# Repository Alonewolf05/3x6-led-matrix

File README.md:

# 3x6-led-matrix
High Power Led Matrix Schematic and PCB Design

Using transistors, shift registers can be used for high power LED applications.

There are 8 pins and micro usb type-b inputs for this board. USB is just for powering the board. No data tranferrings.
ICs are SN74HC595 modules with SOIC127 package.

Pin | Pin Description
------------ | -------------
1 | SRCLK for IC2
2 | SRCLK for IC1
3 | RCLK for IC2
4 | RCLK for IC1
5 | SER for IC2
6 | SER for IC1
7 | GND
8 | +5V

With IC1, rows of led matrix and with IC2 columns of led matrix will be controlled

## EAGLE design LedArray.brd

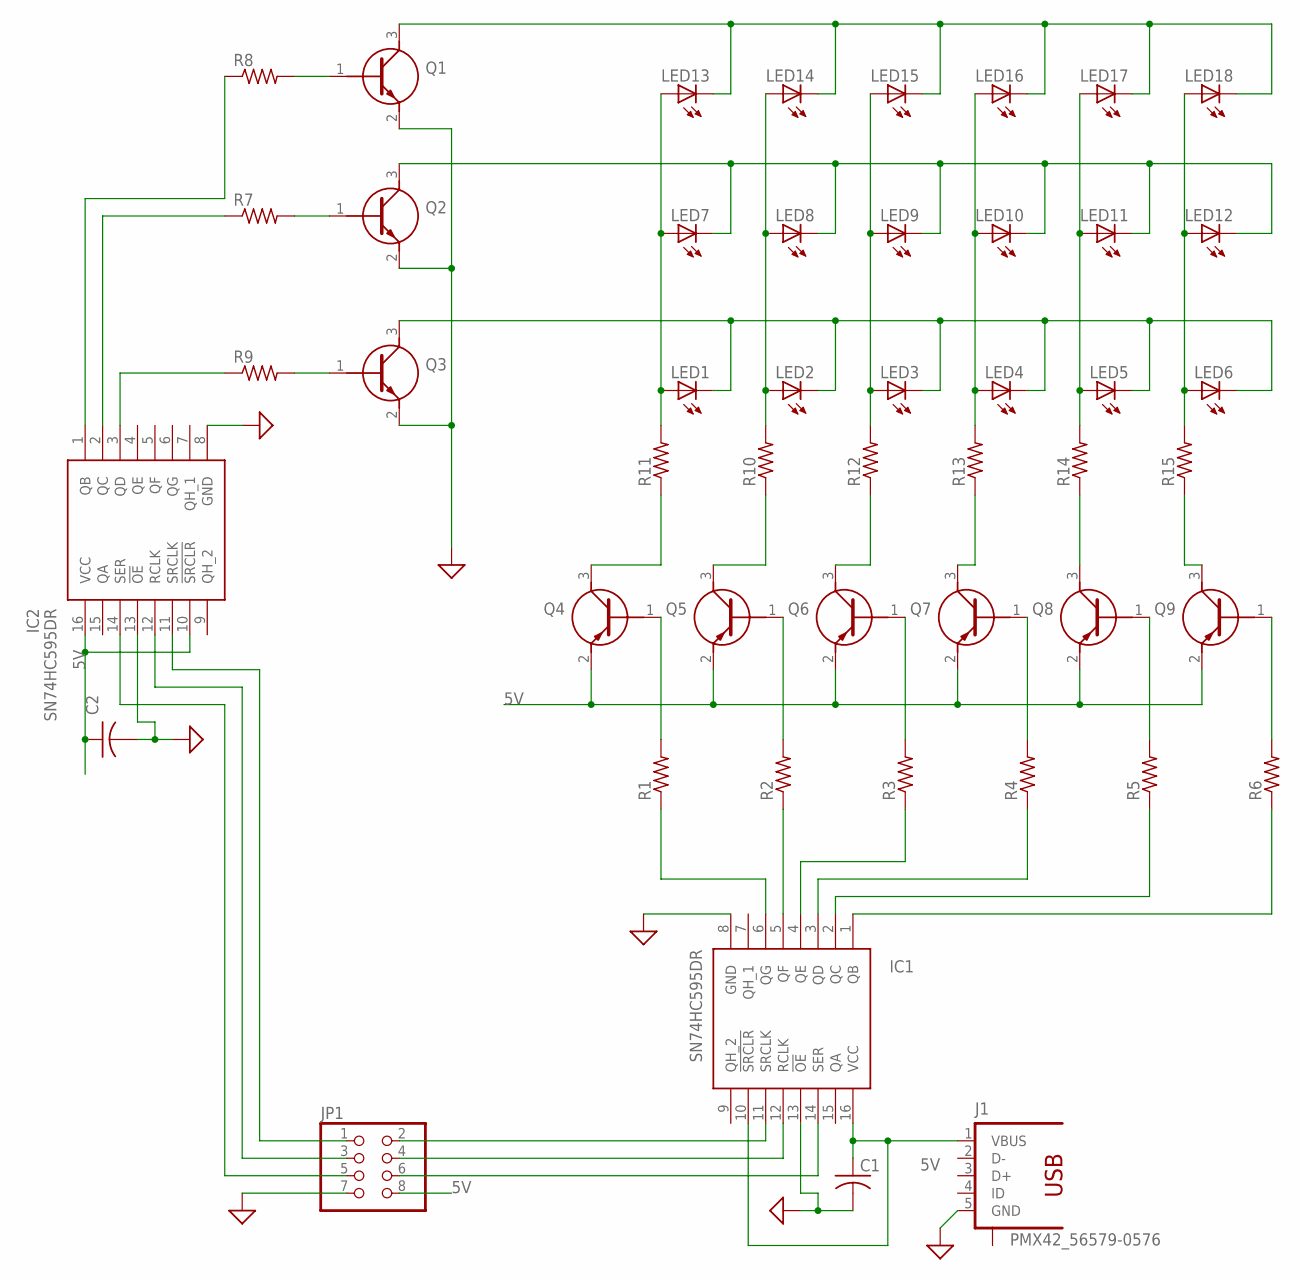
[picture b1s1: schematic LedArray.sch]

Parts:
C1, C2: C-USC1206; C1206
IC1, IC2: SN74HC595DR; SOIC127P600X175-16N
J1: PMX42_56579-0576
JP1: PINHD-2X4; 2X04
LED1, LED2, LED3, LED4, LED5, LED6, LED7, LED8, LED9, LED10, LED11, LED12, LED13, LED14, LED15, LED16, LED17, LED18: LEDSMT1206; 1206
Q1, Q2, Q3: MMBT2222A-G; SOT95P240X115-3N
Q4, Q5, Q6, Q7, Q8, Q9: MMBT2907A-7-F; SOT96P240X100-3N
R1, R2, R3, R4, R5, R6, R7, R8, R9, R10, R11, R12, R13, R14, R15: R-US_R1206; R1206

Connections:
5V: C1.1, C2.1, IC1.10 (!SRCLR), IC1.16 (VCC), IC2.10 (!SRCLR), IC2.16 (VCC), J1.1 (VBUS), JP1.8, Q4.2 (E), Q5.2 (E), Q6.2 (E), Q7.2 (E), Q8.2 (E), Q9.2 (E)
GND: C1.2, C2.2, IC1.8 (GND), IC1.13 (!OE), IC2.8 (GND), IC2.13 (!OE), J1.5 (GND), JP1.7, Q1.2 (E), Q2.2 (E), Q3.2 (E)
unnamed: IC1.1 (QB), R6.1
unnamed: IC1.2 (QC), R5.1
unnamed: IC1.3 (QD), R4.1
unnamed: IC1.4 (QE), R3.1
unnamed: IC1.5 (QF), R2.1
unnamed: IC1.6 (QG), R1.1
unnamed: LED1.A, LED7.A, LED13.A, R11.2
unnamed: LED2.A, LED8.A, LED14.A, R10.2
unnamed: LED3.A, LED9.A, LED15.A, R12.2
unnamed: LED4.A, LED10.A, LED16.A, R13.2
unnamed: LED5.A, LED11.A, LED17.A, R14.2
unnamed: LED6.A, LED12.A, LED18.A, R15.2
unnamed: IC2.1 (QB), R8.1
unnamed: IC2.3 (QD), R9.1
unnamed: Q4.1 (B), R1.2
unnamed: Q5.1 (B), R2.2
unnamed: IC2.2 (QC), R7.1
unnamed: Q6.1 (B), R3.2
unnamed: Q1.1 (B), R8.2
unnamed: Q2.1 (B), R7.2
unnamed: Q3.1 (B), R9.2
unnamed: Q7.1 (B), R4.2
unnamed: Q8.1 (B), R5.2
unnamed: Q9.1 (B), R6.2
unnamed: Q5.3 (C), R10.1
unnamed: Q6.3 (C), R12.1
unnamed: Q7.3 (C), R13.1
unnamed: Q9.3 (C), R15.1
unnamed: Q8.3 (C), R14.1
unnamed: Q4.3 (C), R11.1
unnamed: IC2.14 (SER), JP1.5
unnamed: IC2.12 (RCLK), JP1.3
unnamed: IC2.11 (SRCLK), JP1.1
unnamed: IC1.11 (SRCLK), JP1.2
unnamed: IC1.12 (RCLK), JP1.4
unnamed: IC1.14 (SER), JP1.6
unnamed: LED13.C, LED14.C, LED15.C, LED16.C, LED17.C, LED18.C, Q1.3 (C)
unnamed: LED7.C, LED8.C, LED9.C, LED10.C, LED11.C, LED12.C, Q2.3 (C)
unnamed: LED1.C, LED2.C, LED3.C, LED4.C, LED5.C, LED6.C, Q3.3 (C)

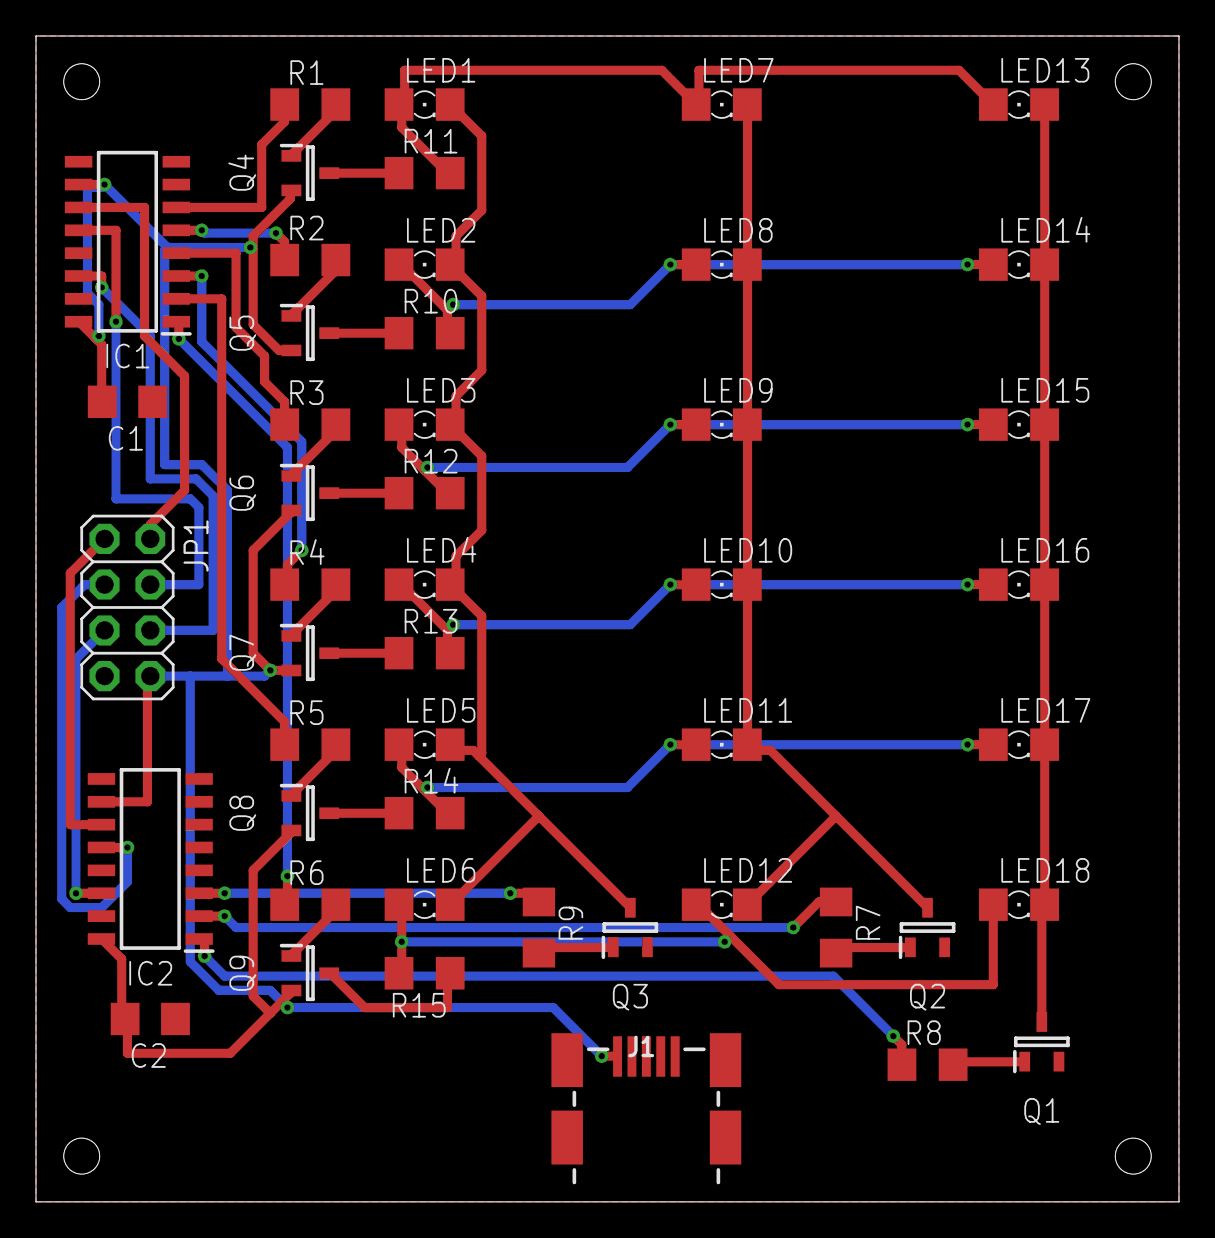
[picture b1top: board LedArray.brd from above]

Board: 2 copper layers, 63.5 x 64.8 mm, 48 parts (0 on the bottom side), 41 nets.

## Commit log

2021-03-22 Add files via upload
    Eagle File
